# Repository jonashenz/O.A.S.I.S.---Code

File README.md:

# O.A.S.I.S. - Obstacle Avoidance Sensory Interface System

O.A.S.I.S. is a wearable haptic feedback system integrated into a belt architecture designed to assist visually impaired individuals in spatial navigation. The system dynamically monitors obstacles at waist-to-chest height using infrared Time-of-Flight (ToF) telemetry and translates physical distance data into deterministic tactile frequency patterns.

This project was developed as a technical thesis (Bereichsübergreifende Projekte - BüP) at the Allgemeine Gewerbeschule Basel.

---

## Technical Features

* **Non-Linear Tactile Scaling:** Implementation of an exponential frequency modulation curve (4 Hz to 12 Hz) within the critical near-field zone to optimize human cognitive perception of hazard proximity.
* **Asynchronous Execution Architecture:** A fully non-blocking, multi-tasking state machine implemented via programmatic timer loops (millis) to ensure real-time execution of sensor polling and PWM output generation without execution lag.
* **Bus Speed Stabilization:** Low-frequency I2C configuration at 20 kHz to guarantee signal integrity and prevent data frames from corrupting across extended wearable wire paths.
* **Digital Signal Conditioning:** Implementation of a software-based Infinite Impulse Response (IIR) low-pass filter to smooth raw telemetry noise and suppress measurement outliers from ambient light interference.

---

## Hardware Architecture

The core architecture is built upon a custom 2-layer printed circuit board (PCB) with a target thickness of 1.6 mm, driven by a portable 3.7V Lithium-Polymer (LiPo) power source.

| Component | Part Number / Specification | Functional Role |
| :--- | :--- | :--- |
| **Microcontroller** | DFRobot FireBeetle 2 ESP32-S3 (DFR0975) | Central processing, I/O routing, and power path control |
| **ToF Sensor Array** | STMicroelectronics VL53L0X | 940 nm infrared distance acquisition via I2C bus |
| **Haptic Actuators** | 3V DC Eccentric Rotating Mass (ERM) | Mechanical vibration pulsing alert generation |
| **Gate Driver Switch** | NDS355AN N-Channel MOSFET | Logic-level low-side gate driver regulation |

### Power Rail Isolation Principle
To prevent critical microcontroller brownout loops caused by sudden inductive current spikes, the ERM vibration motors are wired directly to the unbuffered battery rail (VBAT, 3.7V nominal) via the low-side MOSFET gate switches. This configuration isolates the motor inrush currents entirely from the stabilized 3.3V logic rail powering the ESP32-S3 and the ToF sensor hardware.

---

## Hardware Integration Constraints

### The I2C Peripheral Pin Mapping Conflict
During hardware validation, it was determined that the physical pin designations labeled as SDA (IO1) and SCL (IO2) on the DFRobot FireBeetle 2 board layout cannot be utilized for external I2C peripheral buses. These lines are routed internally to the integrated DC-DC converter regulator circuitry and the GDI display interface. Connecting external sensor buses to these points causes immediate and permanent bus freeze conditions.

To bypass this design constraint, the functional physical I2C bus routing must be explicitly assigned to the alternate pin interface in software configuration:
* **SDA:** Pin 10 (A4)
* **SCL:** Pin 11 (A5)

---

## Control Profile Mapping

The firmware divides physical distance data vectors into deterministic haptic perception bands:

| Operation Zone | Target Distance (d) | Tactile Pulsing Characteristics | Perceptual Intensity |
| :--- | :--- | :--- | :--- |
| **Off** | > 100 cm | Dormant (0% PWM Duty Cycle) | Null |
| **Far (FERN)** | 50 cm - 100 cm | Fixed low-frequency pulsing at 1.0 Hz | Low Noticeability Baseline |
| **Medium (MITTEL)** | 25 cm - 50 cm | Constant paced pulsing at 3.0 Hz | Intermediate Noticeability |
| **Near (NAH)** | 10 cm - 25 cm | Exponential frequency modulation (4.0 Hz - 12.0 Hz) | Dynamic Urgency Ramp |
| **Critical (KRITISCH)**| < 10 cm | Continuous uninterrupted state (100% PWM Duty Cycle) | High Alert Hazard State |

---

## Software Configuration and Environment

The firmware environment is structured and compiled via PlatformIO within the Visual Studio Code integrated development environment.

### Project Structure Directory
```text
├── include/          # Project header directories
├── lib/              # Local peripheral libraries
├── src/
│   └── main.cpp      # Core application source code
└── platformio.ini    # Environment configuration and dependency paths

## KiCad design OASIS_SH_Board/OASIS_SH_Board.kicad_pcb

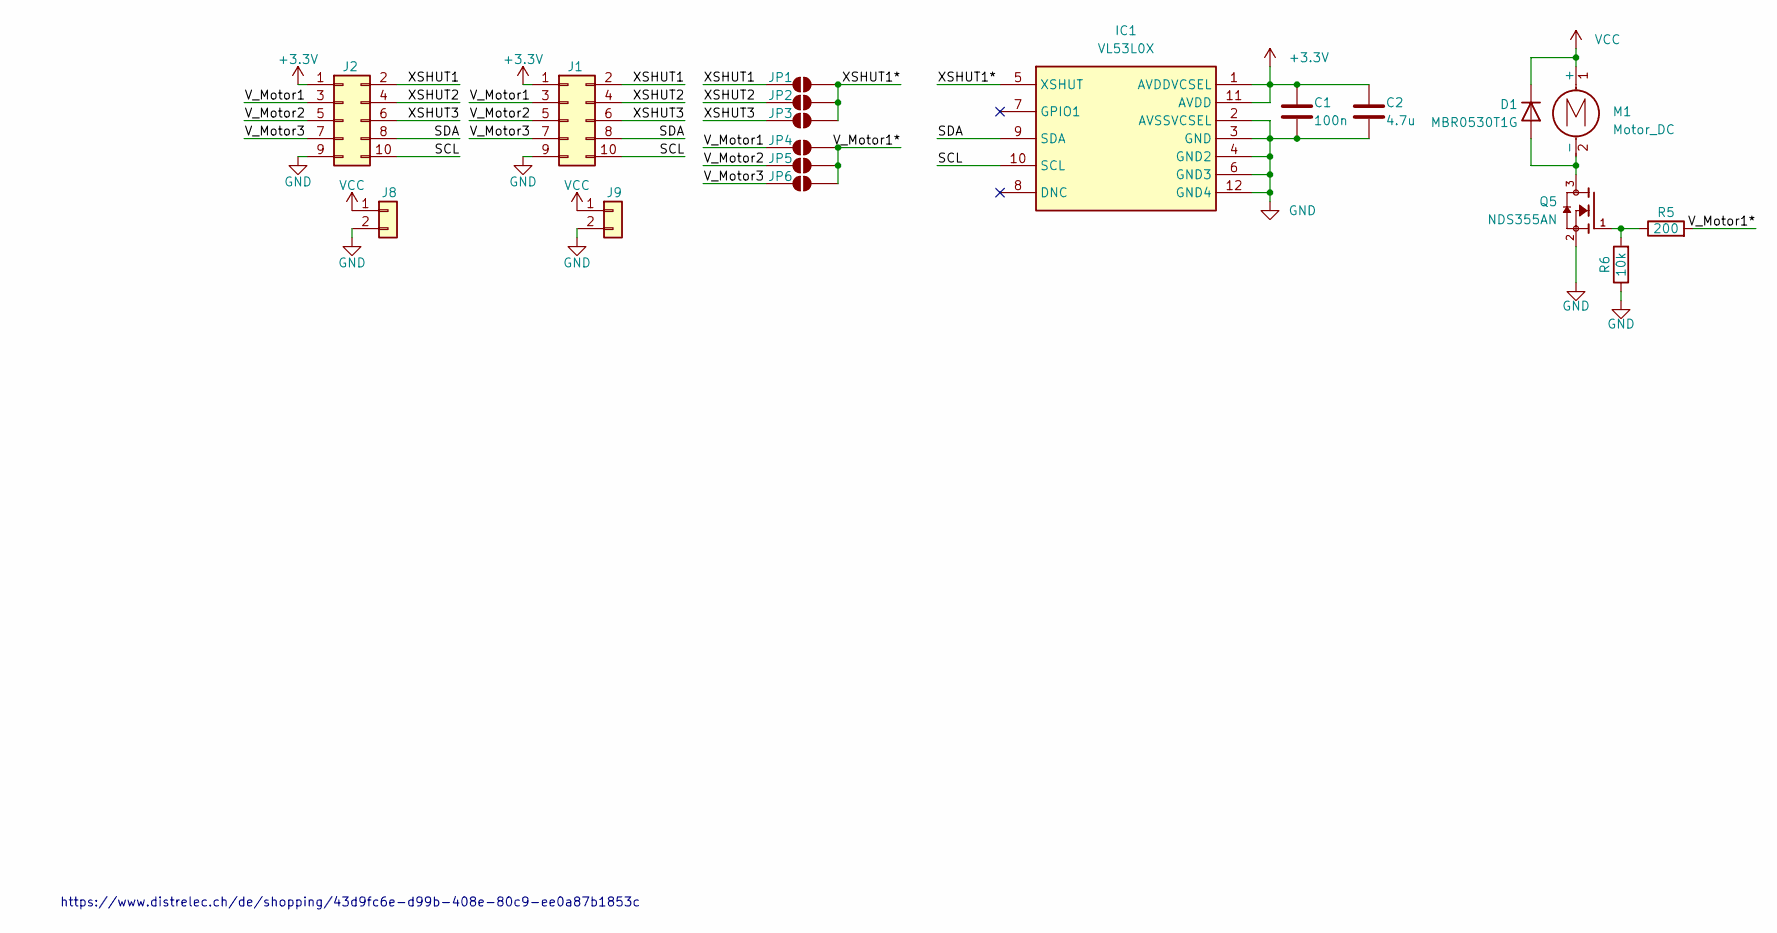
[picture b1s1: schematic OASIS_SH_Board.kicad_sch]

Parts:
C1: 100n; C_0201_0603Metric_Pad0.64x0.40mm_HandSolder
C2: 4.7u; C_Disc_D5.0mm_W2.5mm_P2.50mm
D1: MBR0530T1G; D_SOD-123
IC1: VL53L0X; Manufacturer_Part_Number VL53L0X; Mouser Part Number N/A
J1, J2: Conn_02x05_Top_Bottom; PinHeader_2x05_P2.54mm_Vertical
J8, J9: Conn_01x02; PinHeader_1x02_P2.54mm_Vertical
JP1, JP2, JP3, JP4, JP5, JP6: SolderJumper_2_Open; PinHeader_1x02_P2.54mm_Vertical
M1: Motor_DC; PinHeader_1x02_P2.54mm_Vertical
Q5: NDS355AN; SOT95P251X112-3N; PARTREV 3
R5: 200; R_0201_0603Metric_Pad0.64x0.40mm_HandSolder
R6: 10k; R_0201_0603Metric_Pad0.64x0.40mm_HandSolder

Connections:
+3.3V: C1.1, C2.1, IC1.1 (AVDDVCSEL), IC1.11 (AVDD), J1.1, J2.1
/SCL: IC1.10 (SCL), J1.10, J2.10
/SDA: IC1.9 (SDA), J1.8, J2.8
/V_Motor1: J1.3, J2.3, JP4.1 (A)
/V_Motor1*: JP4.2 (B), JP5.2 (B), JP6.2 (B), R5.2
/V_Motor2: J1.5, J2.5, JP5.1 (A)
/V_Motor3: J1.7, J2.7, JP6.1 (A)
/XSHUT1: J1.2, J2.2, JP1.1 (A)
/XSHUT1*: IC1.5 (XSHUT), JP1.2 (B), JP2.2 (B), JP3.2 (B)
/XSHUT2: J1.4, J2.4, JP2.1 (A)
/XSHUT3: J1.6, J2.6, JP3.1 (A)
GND: C1.2, C2.2, IC1.2 (AVSSVCSEL), IC1.3 (GND), IC1.4 (GND2), IC1.6 (GND3), IC1.12 (GND4), J1.9, J2.9, J8.2, J9.2, Q5.2, R6.1
unnamed: D1.2 (A), M1.2 (-), Q5.3
unnamed: Q5.1, R5.1, R6.2
VCC: D1.1 (K), J8.1, J9.1, M1.1 (+)

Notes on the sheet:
https://www.distrelec.ch/de/shopping/43d9fc6e-d99b-408e-80c9-ee0a87b1853c

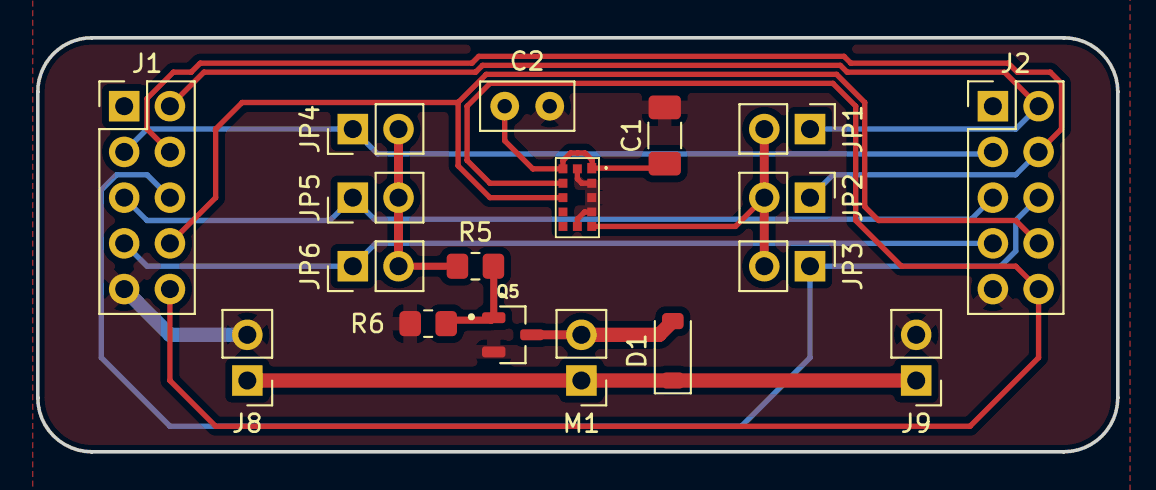
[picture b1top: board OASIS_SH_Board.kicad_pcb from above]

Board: 2 copper layers, 60.0 x 23.0 mm, 18 parts (0 on the bottom side), 15 nets.

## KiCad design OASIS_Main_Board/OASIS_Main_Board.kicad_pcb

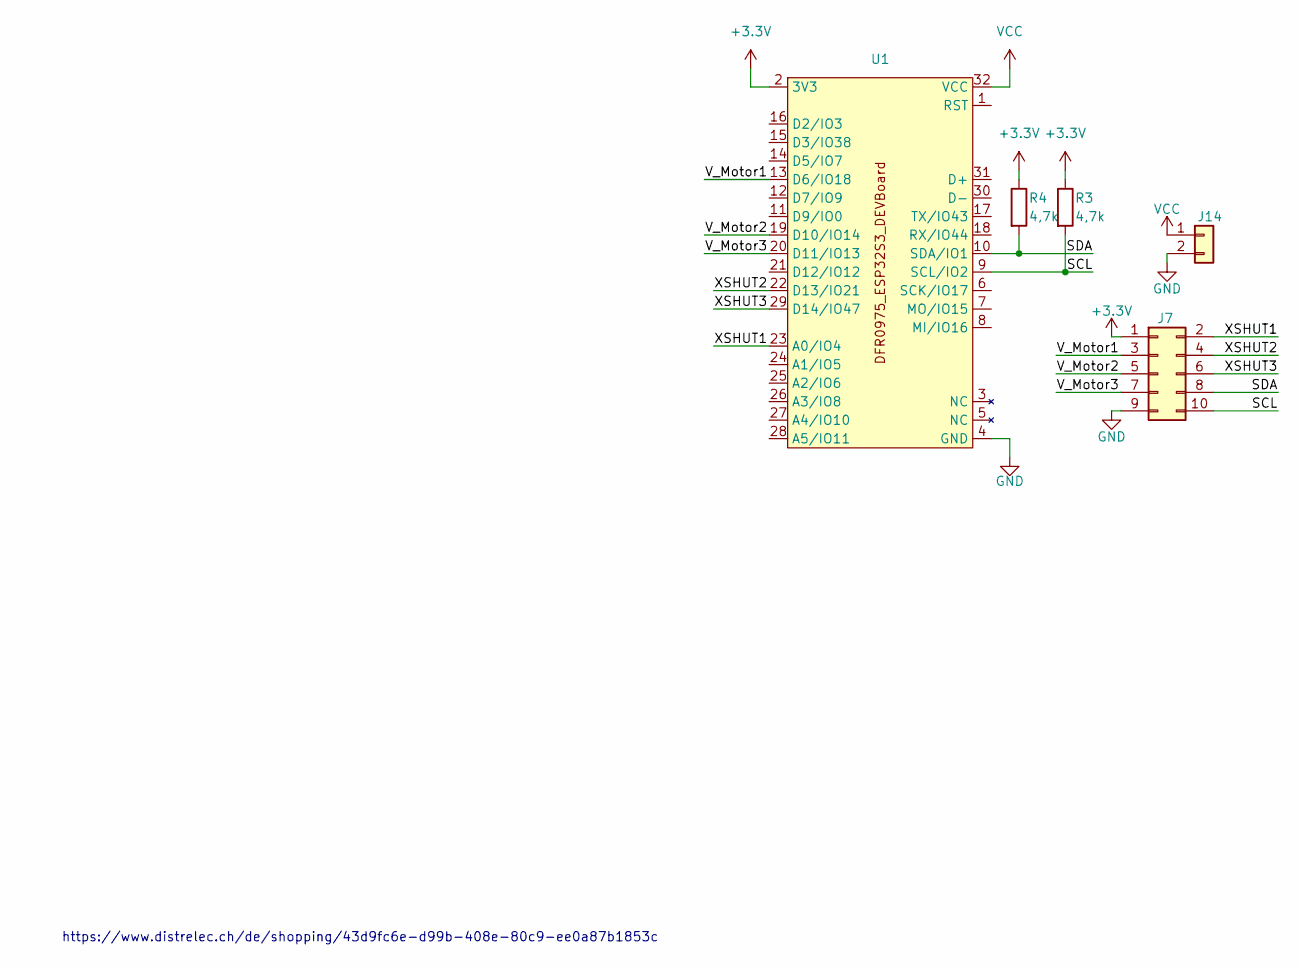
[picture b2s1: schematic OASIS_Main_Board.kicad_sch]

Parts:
J7: Conn_02x05_Top_Bottom; PinHeader_2x05_P2.54mm_Vertical
J14: Conn_01x02; PinHeader_1x02_P2.54mm_Vertical
R3, R4: 4,7k; R_0201_0603Metric_Pad0.64x0.40mm_HandSolder
U1: DFR0975_ESP32S3_DEVBoard

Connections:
+3.3V: J7.1, R3.1, R4.1, U1.2 (3V3)
/SCL: J7.10, R3.2, U1.9 (SCL/IO2)
/SDA: J7.8, R4.2, U1.10 (SDA/IO1)
/V_Motor1: J7.3, U1.13 (D6/IO18)
/V_Motor2: J7.5, U1.19 (D10/IO14)
/V_Motor3: J7.7, U1.20 (D11/IO13)
/XSHUT1: J7.2, U1.23 (A0/IO4)
/XSHUT2: J7.4, U1.22 (D13/IO21)
/XSHUT3: J7.6, U1.29 (D14/IO47)
GND: J7.9, J14.2, U1.4 (GND)
VCC: J14.1, U1.32 (VCC)

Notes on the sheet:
https://www.distrelec.ch/de/shopping/43d9fc6e-d99b-408e-80c9-ee0a87b1853c

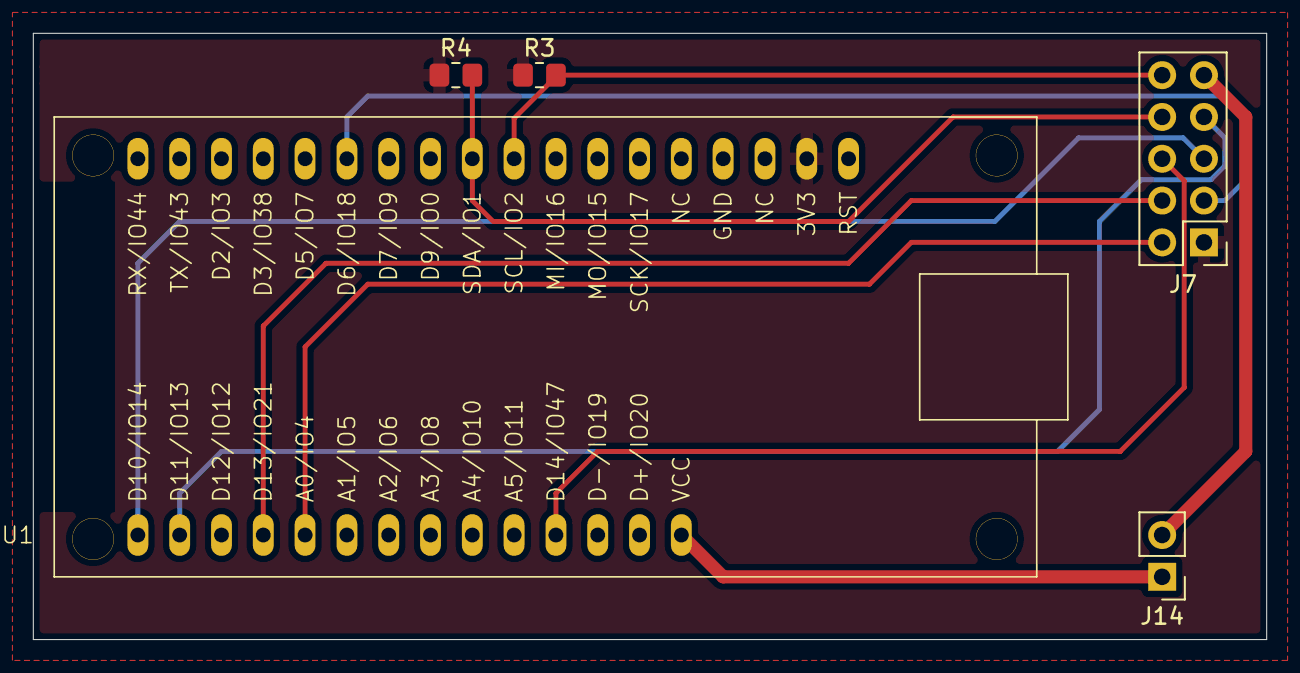
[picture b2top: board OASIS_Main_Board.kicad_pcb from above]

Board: 2 copper layers, 74.9 x 36.8 mm, 5 parts (0 on the bottom side), 11 nets.

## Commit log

2026-06-11 README with project details and specifications
    Expanded project description and technical features in README.
2026-06-11 Add hardware design files
2026-06-11 Update README with image and project details
    Added an image and enhanced project description.
2026-06-11 Add Abschlussbericht
2026-06-11 add presentation
2026-06-11 OASIS_presentation.html to docs/OASIS_presentation.html
2026-06-11 Upload project datasheets
2026-06-11 Add MIT License to the project
2026-06-11 Delete docs/Abschlussbericht_Buep_Jonas.docx
    false title
2026-06-11 docs: correct report title to Final Report
    changed title and added a pdf
